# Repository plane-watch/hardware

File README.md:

# Plane Watch hardware

Open hardware designs from Plane Watch for receiving and decoding aircraft surveillance signals.

<div style="text-align: center;"></div>

## Hardware projects

| Project | Preview Image | Description |
| ------- | ------------- | ----------- |
| [ADSBoost](adsboost/README.md) |  | A receive-only, bias-tee-powered low-noise amplifier and SAW filter module for 1,090 MHz ADS-B and Mode S reception. ADSBoost is designed to be installed close to the antenna; the current prototype is awaiting assembly and performance testing. |
| [Plane Watcher](planewatcher/README.md) |  | An open source, hardware-based ADS-B receiver and decoder for the HelloFPGA Smart ZYNQ SL. Plane Watcher combines a dual-stage RF front end, log detector, ADC and GNSS timing to support FPGA message decoding and accurate MLAT timestamping. |

## License

Unless a project or file explicitly states otherwise, all original hardware design files in this repository are licensed under the [CERN Open Hardware Licence Version 2 – Strongly Reciprocal (CERN-OHL-S-2.0)](LICENSE).

The CERN-OHL-S-2.0 permits commercial use, but its reciprocal requirements apply when covered source or products based on it are distributed. Alternative commercial licensing is available for organisations that need different terms.

In short: you may use and modify the designs privately. If you distribute modified source or products based on them, the CERN-OHL-S-2.0 requirements apply.

## Third-party materials disclaimer

This repository may include third-party datasheets, application notes and other technical documentation. These materials remain the copyright of their respective owners, are not covered by the repository's hardware licence, and are included solely to assist development and interoperability of the hardware projects.

If you are a copyright holder and have concerns about material included here, please open an issue or contact the maintainers.

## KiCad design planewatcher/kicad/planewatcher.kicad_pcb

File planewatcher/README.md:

# plane watcher

The **plane watcher** is our attempt at creating an open source, hardware-based ADS-B receiver and decoder. It is a hat/cape/shield for a [HelloFPGA Smart ZYNQ SL](http://www.hellofpga.com/index.php/2023/05/10/smart-zynq-sl/) board.

The goal of the project is to make a reasonably priced yet high-quality ADS-B receiver for hobbyists. It is designed to support accurate MLAT timestamping using GNSS timing and message decoding in the FPGA.

This repository contains the hardware design. The FPGA gateware and software live in the [plane-watch/plane-watcher](https://github.com/plane-watch/plane-watcher) repository.

<div style="text-align: center;"></div>

## Status

Prototype board revision 1.3 is the latest fabricated and tested revision. Production board revision 1.4 is still being refined and has not yet been fabricated or validated.

### Prototype Board Revision 1.2

The first fabricated prototype worked, but had a few issues:

- The SMA connector for the 1090 MHz RF input fouled on the RJ45 Ethernet connector of the FPGA board. For proto 1.3, the RF and GPS antenna connectors have been swapped to U.FL. We will use pigtails to panel-mount SMA connectors.
- The ADL5513 log-detector output was not strong enough to drive the AD8138 ADC driver gain/feedback network directly. Increasing the gain/feedback resistor values from 499 Ω to 4.7 kΩ fixed this on the prototype. In proto 1.3, the ADL5513 output is also buffered.
- We did not have component footprints to tweak the ADL5513 output slope. These have been added to proto 1.3 to allow further refinement if required.
- The 1PPS LED was way too bright on the prototype, so this has been dimmed for proto 1.3.
- The ADL5513 TADJ trimmer network was too high impedance (I should've read the data sheet better) and did not appear to make any difference whatsoever. This has been replaced with a simple voltage divider set to around 0.86 V, in line with the datasheet guidance.

Regardless of the issues, we observed a reception range of approximately 320 km.

### Prototype Board Revision 1.3

In addition to fixing the issues above, proto 1.3 includes some functionality and layout changes:

- More unpopulated component footprints have been added to allow tweaking/refinement:
  - ADL5513 log-detector slope adjustment voltage divider.
  - AD8138 ADC driver feedback capacitors.
  - Five 0402 pi-pad matching networks along the RF path: one on each side of both LNA stages, and one at the ADL5513 RF input. These enable us refine the 1090 MHz matching and compensate for real-world PCB and component parasitics.
    - The first footprint was populated with additional shunt inductance to greatly improve RF performance.
  - Other tweaking footprints along the ADC signal path.
- The ADL5513 log-detector output is buffered by a high-speed ADA4807-1 op-amp for more robust operation with weak signals, and to decouple it from the AD8138 input network.
- The buffered log-detector output is also fed into a first-order low-pass filter at approximately 0.072 Hz to produce a slow-moving analog baseline. This heavily attenuates short ADS-B pulse bursts, but sustained RF traffic can still affect the baseline. The baseline is buffered by an OPA320 and applied to the AD8138 ADC driver input network, offsetting the detector output before digitisation and improving the usable ADC range for weak pulses.
- RF_IN and GPS antenna connectors have been swapped from SMA to U.FL allowing them to be fitted by the manufacturer, making hand assembly easier.
- A software-controlled bias tee has been added. This can supply around 4.5 V to the RF_IN connector, current-limited to approximately 300 mA. LEDs have been added to show whether bias tee is enabled/disabled, and to show if overcurrent disable has been activated.
- A GNSS-disciplined 1PPS timing output has been added. This is a buffered copy of the LEA-M8T TIMEPULSE signal, provided on a 50 Ω source-terminated U.FL connector. The centre pin carries an active-high pulse and the shell is connected to ground. The output is approximately 0 to 4.5 V into a high-impedance load, or approximately 0 to 2 V into a 50 Ω terminated load. The rising edge should be treated as the timing reference.
- Some discrete resistors have been replaced with resistor arrays to reduce the BoM and make hand assembly easier.
- The ADC supply, reference and VOCM networks have been reworked in an attempt to reduce noise, including additional bypassing, ferrite isolation and improved grounding.
- Selectable REFSENSE links allow the ADC input range to be configured for 1 Vpp or 2 Vpp.
- PCB grounding and sensitive-node isolation have been revised with additional via stitching, shorter reference routing and copper keepouts.
- Additional high-frequency bypassing has been added to keep the bias-tee supply side at RF ground.
- Re-routed ADC input differential pair to remove vias/crossovers & remove skew. The ADC output will need to be negated in software.

Compared to proto 1.2 (blue), the range for proto 1.3 (red) has improved by approximately 70km:

Proto 1.3 (red) performance is roughly on-par with a commercial [Jetvision Radarcape](https://radarcape.com) unit (blue):

## Hardware overview

The design has the following main components and interfaces:

| Function | Implementation |
| --- | --- |
| RF input | 1090 MHz ADS-B, U.FL connector |
| RF front end | Two LNA and SAW filter stages |
| Log detector | ADL5513 |
| Baseband buffers | ADA4807-1 fast-path buffer and OPA320 slow-baseline buffer |
| ADC driver | AD8138 |
| ADC | AD9203, 10-bit, up to 40 MSPS |
| GNSS timing | LEA-M8T with FPGA and external 1PPS outputs |
| Bias tee | Software-controlled, approximately 4.5 V at approximately 300 mA with over-current protection |
| Local power | LT3045 low-noise 3.3 V RF/analog supply |
| FPGA carrier | HelloFPGA Smart ZYNQ SL |

## Connections

| Reference | Connection                 | Connector / pinout                                     | Function                                                                                                                    | Voltage and current                                                                                                                                                                                                                                         |
|-----------|----------------------------|--------------------------------------------------------|-----------------------------------------------------------------------------------------------------------------------------|-------------------------------------------------------------------------------------------------------------------------------------------------------------------------------------------------------------------------------------------------------------|
| **J1**    | **1PPS output**            | U.FL; centre = signal, shell = ground                  | Buffered, non-inverting GNSS TIMEPULSE output. Configure for active-high 1PPS with the rising edge as the timing reference. | With a nominal 4.5 V supply: approximately **0–4.5 V into high impedance**, or **0–2.0 V into 50 Ω**, delivering approximately **40 mA while high**. Includes a 49.9 Ω series resistor; total source resistance is approximately 65 Ω including the driver. |
| **J2**    | **1090 MHz RF input**      | U.FL; centre = RF and optional DC bias, shell = ground | Antenna input for the ADS-B receiver; nominal 50 Ω RF interface.                                                            | Software-controlled bias tee supplies approximately **4.5 V** when enabled. Current-limit threshold is approximately **320 mA**. Sustained overload causes latched shutdown.                                                                                |
| **J6**    | **GNSS antenna input**     | U.FL; centre = RF and DC bias, shell = ground          | Antenna input to the LEA-M8T GNSS receiver; nominal 50 Ω RF interface.                                                      | Active-antenna power is provided through the LEA-M8T antenna-supply circuit.                                                                                                                                                                                |
| **J4**    | **FPGA bank 33 interface** | 40-pin header                                          | Carries the ADC sample clock, 10-bit ADC data, overrange indication, RGB LED controls and regulator power-good signal.      | Receives nominal **3.3 V** on pins **37–38** and approximately **4.5 V FPGA_VCC** on pins **39–40**; ground on pins **35–36**. The 4.5 V input feeds the local regulator (for RF and ADC analog side) and 1PPS driver.                                      |
| **J5**    | **FPGA bank 35 interface** | 40-pin header                                          | Carries GNSS serial/control/timing signals, EEPROM I²C, and bias-tee enable/fault signals.                                  | Receives approximately **4.5 V FPGA_VCC** on pins **1–2** and nominal **3.3 V** on pins **3–4**; ground on pins **5–6**. Supplies the bias tee, GNSS and EEPROM circuits. Available current depends on the carrier board.                                   |

## Blinkenlights

The board currently has 8 LEDs, which are used as follows:

| LED  | Type                            | Purpose                                                                                                             |
|------|---------------------------------|---------------------------------------------------------------------------------------------------------------------|
| LED1 | RGB, software controlled        | **System status:**</br>red (FIFO-full latched) > amber (decoder disabled) > green heartbeat (PL alive and clocking) |
| LED2 | RGB, software controlled        | **DF17 activity**</br>green flash per DF17 extended squitter                                                        |
| LED3 | RGB, software controlled        | **DF11/valid**</br>blue flash per DF11 / accepted message                                                           |
| LED4 | RGB, software controlled        | **Decode health**</br>red when invalid DFs outpace accepted messages, else green while messages flow                |
| LED5 | RGB, software controlled        | reserved for PS override (app/feeder status)                                                                        |
| LED6 | "Pink" (looks white), hardwired | 1PPS from GNSS module (when locked)                                                                                 |
| LED7 | Green, hardwired                | Lit when bias-tee enabled                                                                                           |
| LED8 | Red, hardwired                  | Bias-tee over-current shutdown or thermal shutdown                                                                  |

## Design

The design consists of the following parts:

### RF Input

The signal from the antenna is amplified and filtered using two stages of LNA amplification and SAW filters centred on 1090 MHz.

A switchable bias tee power supply can apply approximately 4.5 V at up to approximately 300 mA to the RF_IN connector.

LED7 (green) indicates bias-tee is enabled.
LED8 (red) indicates an overcurrent shutdown of bias-tee.

### Log Detector

The amplified and filtered RF signal is fed into an ADL5513 log detector, which produces a voltage proportional to the logarithm of the RF input power. With an oscilloscope on its output, we can see the raw ADS-B pulses and decode them by hand.

### ADC Driver

The ADL5513 log-detector output is buffered with a high-speed ADA4807-1 op-amp to isolate it from the ADC driver input network and provide a robust baseband signal. Without the buffer, the output of the log detector is too weak for the gain/feedback network surrounding the AD8138.

The ADC uses a differential input. To drive it, the buffered baseband signal is split:

- Through the gain/input resistor network into the AD8138 positive input summing node.
- Into a first-order low-pass filter at approximately 0.072 Hz, producing a slow-moving analog baseline with short ADS-B pulse bursts heavily attenuated. This baseline is then buffered by an OPA320 to decouple it from the ADC driver input network and applied through the gain/input resistor network into the AD8138 negative input summing node.

The AD8138 produces a differential output proportional to the difference between the instantaneous log-detector output and the slow noise-floor estimate.

### ADC

The differential output of the ADC driver is fed into an AD9203 10-bit, 40 MSPS ADC. The ADC input range can be configured for 1 Vpp or 2 Vpp using selectable REFSENSE links. By default, 2 Vpp is used to give the largest dynamic range. The FPGA supplies the sample clock and receives the digitised output.

### GNSS Timing

The LEA-M8T GNSS timing receiver provides its TIMEPULSE signal to the FPGA for timestamping. Proto 1.3 also buffers this signal for an external, source-terminated 1PPS output and a status LED (LED6).

### EEPROM

The board contains a 16K I²C EEPROM. The EEPROM data is written once at assembly time and read back at boot-time to set board details such as MAC address, serial number, credentials, etc.

### Power

The power supplies are split in an attempt to reduce noise on the RF & ADC supply.

#### RF & ADC

The RF and analog ADC sections are powered from the approximately 4.5 V FPGA_VCC rail provided by the carrier board (5V from the USB-C connector, through a Schottky diode). The input has resettable overcurrent and transient protection. A ferrite-filtered LT3045-1 linear regulator generates the local low-noise 3.3 V RF/analog supply, with additional ferrite isolation and local bypassing around the ADC.

The ADC digital power is fed directly from the FPGA board 3V3 rail.

#### Bias-Tee, GNSS & EEPROM

These are powered directly from the FPGA board:

- Bias-Tee current is supplied by the approximately 4.5 V FPGA_VCC rail
- The GNSS module is powered directly from the FPGA board 3V3 rail. The 1PPS output is powered from the approximately 4.5 V FPGA_VCC rail via a MOSFET driver.
- The EEPROM is powered directly from the FPGA board 3V3 rail.

### FPGA

The FPGA gateware samples the ADC output, detects and timestamps ADS-B pulses, and converts them into usable messages. The gateware and supporting software are developed in the [plane-watch/plane-watcher](https://github.com/plane-watch/plane-watcher) repository.

## Attributions

- [“1.09 GHz Mode-S Receiver Design and
  VHF Radar Antenna Characterization”, Senior Thesis in Electrical Engineering, Dabin Zhang](https://www.ideals.illinois.edu/items/47640/bitstreams/139976/data.pdf).
- [Project “ADS-B Receiver and Decoder” presentation by Günter Köllner, DL4MEA](https://www.qsl.net/dl4mea/fpgaadsb/Koellner_Projekt-ADSB3.pdf).
- The [Open Source Hardware gear logo](https://oshwa.org/resources/open-source-hardware-logo/) was designed by Macklin Chaffee and is licensed CC-SA.
- “Dickbutt” appears courtesy of [K.C. Green](https://kcgreendotcom.com/). RF performance gains are unverified.

## License

The hardware design files are licensed under the [CERN Open Hardware Licence Version 2 – Strongly Reciprocal (CERN-OHL-S-2.0)](LICENSE).

The CERN-OHL-S-2.0 permits commercial use, but its reciprocal requirements apply when covered source or products based on it are distributed.

Alternative commercial licensing is available for companies that need different terms.

TL;DR: You can use and modify the design privately. If you distribute modified source or products based on it, the CERN-OHL-S-2.0 requirements apply. If those terms do not work for you, talk to us.

## Notice

This repository may include third-party datasheets, application notes, and technical documentation.

Such materials remain the copyright of their respective owners and are included solely to assist development and interoperability of this project.

If you are a copyright holder and have concerns regarding included materials, please open an issue or contact the maintainers.

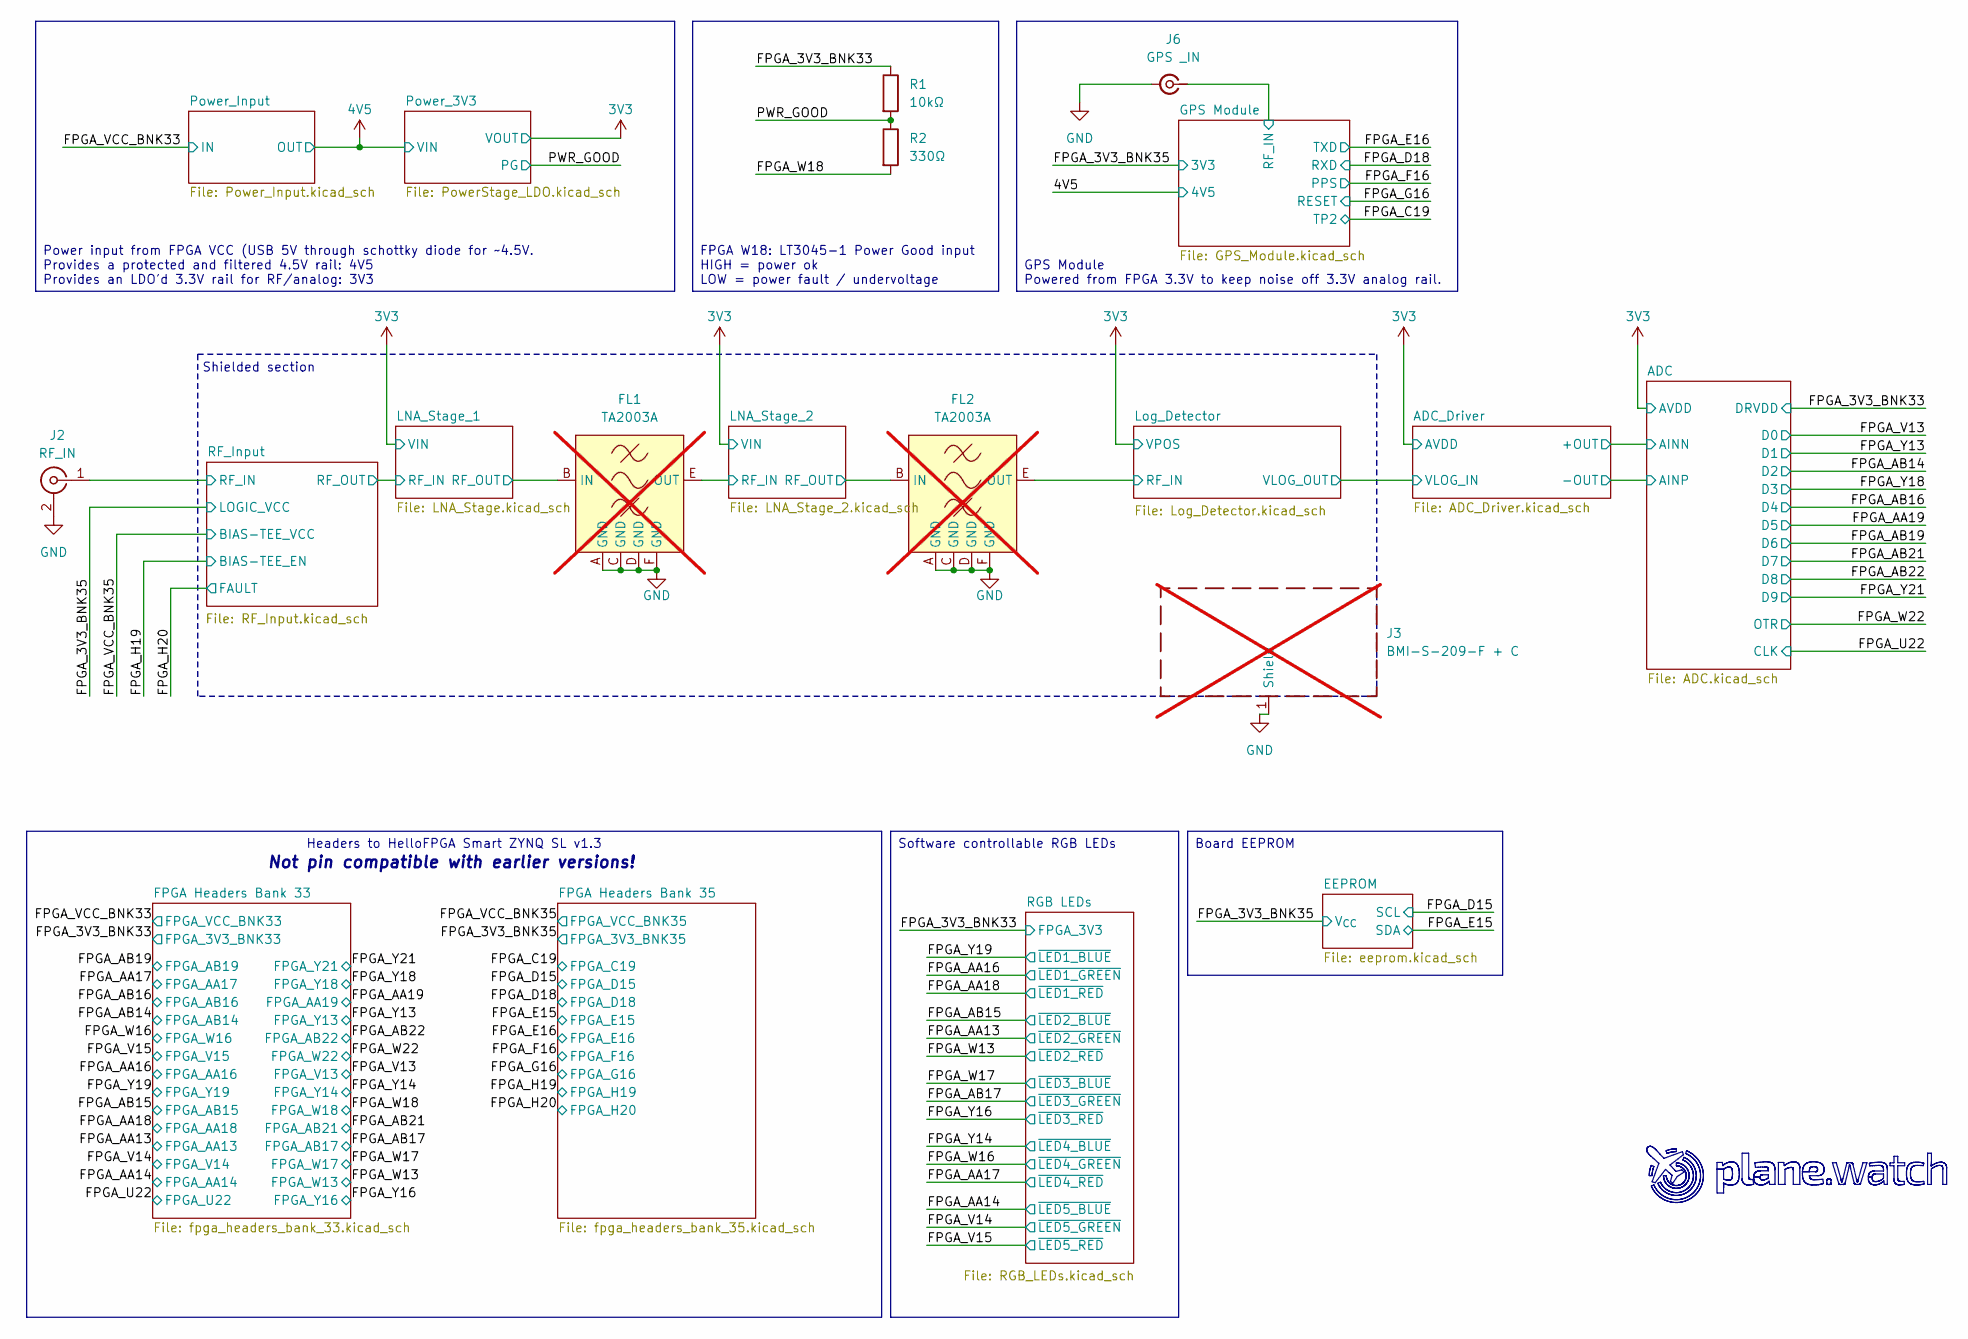
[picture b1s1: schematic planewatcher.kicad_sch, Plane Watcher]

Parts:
FL1, FL2: TA2003A; FL_Tai-Saw_TA2003A; MPN TA2003A; not fitted
J2: RF_IN; U.FL_Hirose_U.FL-R-SMT-1_Vertical; MPN U.FL-R-SMT-1; LCSC C88374
J3: BMI-S-209-F + C; Laird_Technologies_BMI-S-209-F_29.36x18.50mm; MPN BMI-S-209-F + BMI-S-209-C; not fitted
J6: GPS _IN; U.FL_Hirose_U.FL-R-SMT-1_Vertical; MPN U.FL-R-SMT-1; LCSC C88374
R1: 10kΩ; R_0402_1005Metric; MPN ERA-2AEB103X; LCSC C191915
R2: 330Ω; R_0402_1005Metric; MPN RT0402FRE07330RL; LCSC C854274

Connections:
/FPGA_3V3_BNK33: R1.1; also elsewhere on the board
/FPGA_W18: R2.2; also elsewhere on the board
/GPS Module/RF_IN: J6.1 (In); also elsewhere on the board
/LNA_Stage_1/RF_OUT: FL1.B (IN); also elsewhere on the board
/LNA_Stage_2/RF_IN: FL1.E (OUT); also elsewhere on the board
/LNA_Stage_2/RF_OUT: FL2.B (IN); also elsewhere on the board
/Log_Detector/RF_IN: FL2.E (OUT); also elsewhere on the board
/PWR_GOOD: R1.2, R2.1; also elsewhere on the board
/RF_Input/RF_IN: J2.1 (In); also elsewhere on the board
GND: FL1.A (GND), FL1.C (GND), FL1.D (GND), FL1.F (GND), FL2.A (GND), FL2.C (GND), FL2.D (GND), FL2.F (GND), J2.2 (Ext), J3.1 (Shield_1), J6.2 (Ext); also elsewhere on the board

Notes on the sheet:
Shielded section
Not pin compatible with earlier versions!
Board EEPROM
FPGA W18: LT3045-1 Power Good input HIGH = power ok LOW = power fault / undervoltage
Power input from FPGA VCC (USB 5V through schottky diode for ~4.5V. Provides a protected and filtered 4.5V rail: 4V5 Provides an LDO'd 3.3V rail for RF/analog: 3V3
GPS Module Powered from FPGA 3.3V to keep noise off 3.3V analog rail.
Headers to HelloFPGA Smart ZYNQ SL v1.3
Software controllable RGB LEDs

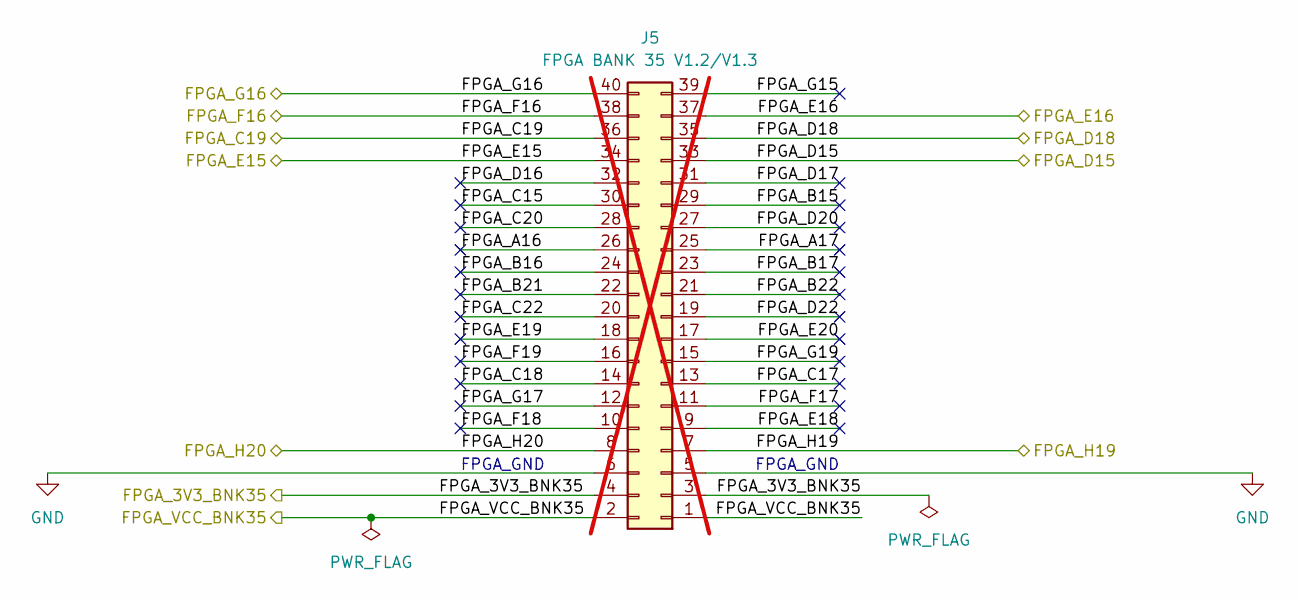
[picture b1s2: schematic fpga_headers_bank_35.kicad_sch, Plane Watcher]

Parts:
J5: FPGA BANK 35 V1.2/V1.3; PinHeader_2x20_P2.54mm_Vertical; MPN TSW-120-07-L-D; LCSC C5968215; not fitted

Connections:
/FPGA Headers Bank 35/FPGA_A16: J5.26
/FPGA Headers Bank 35/FPGA_A17: J5.25
/FPGA Headers Bank 35/FPGA_B15: J5.29
/FPGA Headers Bank 35/FPGA_B16: J5.24
/FPGA Headers Bank 35/FPGA_B17: J5.23
/FPGA Headers Bank 35/FPGA_B21: J5.22
/FPGA Headers Bank 35/FPGA_B22: J5.21
/FPGA Headers Bank 35/FPGA_C15: J5.30
/FPGA Headers Bank 35/FPGA_C17: J5.13
/FPGA Headers Bank 35/FPGA_C18: J5.14
/FPGA Headers Bank 35/FPGA_C20: J5.28
/FPGA Headers Bank 35/FPGA_C22: J5.20
/FPGA Headers Bank 35/FPGA_D16: J5.32
/FPGA Headers Bank 35/FPGA_D17: J5.31
/FPGA Headers Bank 35/FPGA_D20: J5.27
/FPGA Headers Bank 35/FPGA_D22: J5.19
/FPGA Headers Bank 35/FPGA_E18: J5.9
/FPGA Headers Bank 35/FPGA_E19: J5.18
/FPGA Headers Bank 35/FPGA_E20: J5.17
/FPGA Headers Bank 35/FPGA_F17: J5.11
/FPGA Headers Bank 35/FPGA_F18: J5.10
/FPGA Headers Bank 35/FPGA_F19: J5.16
/FPGA Headers Bank 35/FPGA_G15: J5.39
/FPGA Headers Bank 35/FPGA_G17: J5.12
/FPGA Headers Bank 35/FPGA_G19: J5.15
/FPGA_3V3_BNK35: J5.3, J5.4; also elsewhere on the board
/FPGA_C19: J5.36; also elsewhere on the board
/FPGA_D15: J5.33; also elsewhere on the board
/FPGA_D18: J5.35; also elsewhere on the board
/FPGA_E15: J5.34; also elsewhere on the board
/FPGA_E16: J5.37; also elsewhere on the board
/FPGA_F16: J5.38; also elsewhere on the board
/FPGA_G16: J5.40; also elsewhere on the board
/FPGA_H19: J5.7; also elsewhere on the board
/FPGA_H20: J5.8; also elsewhere on the board
/FPGA_VCC_BNK35: J5.1, J5.2; also elsewhere on the board
GND: J5.5, J5.6; also elsewhere on the board

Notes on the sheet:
FPGA_GND

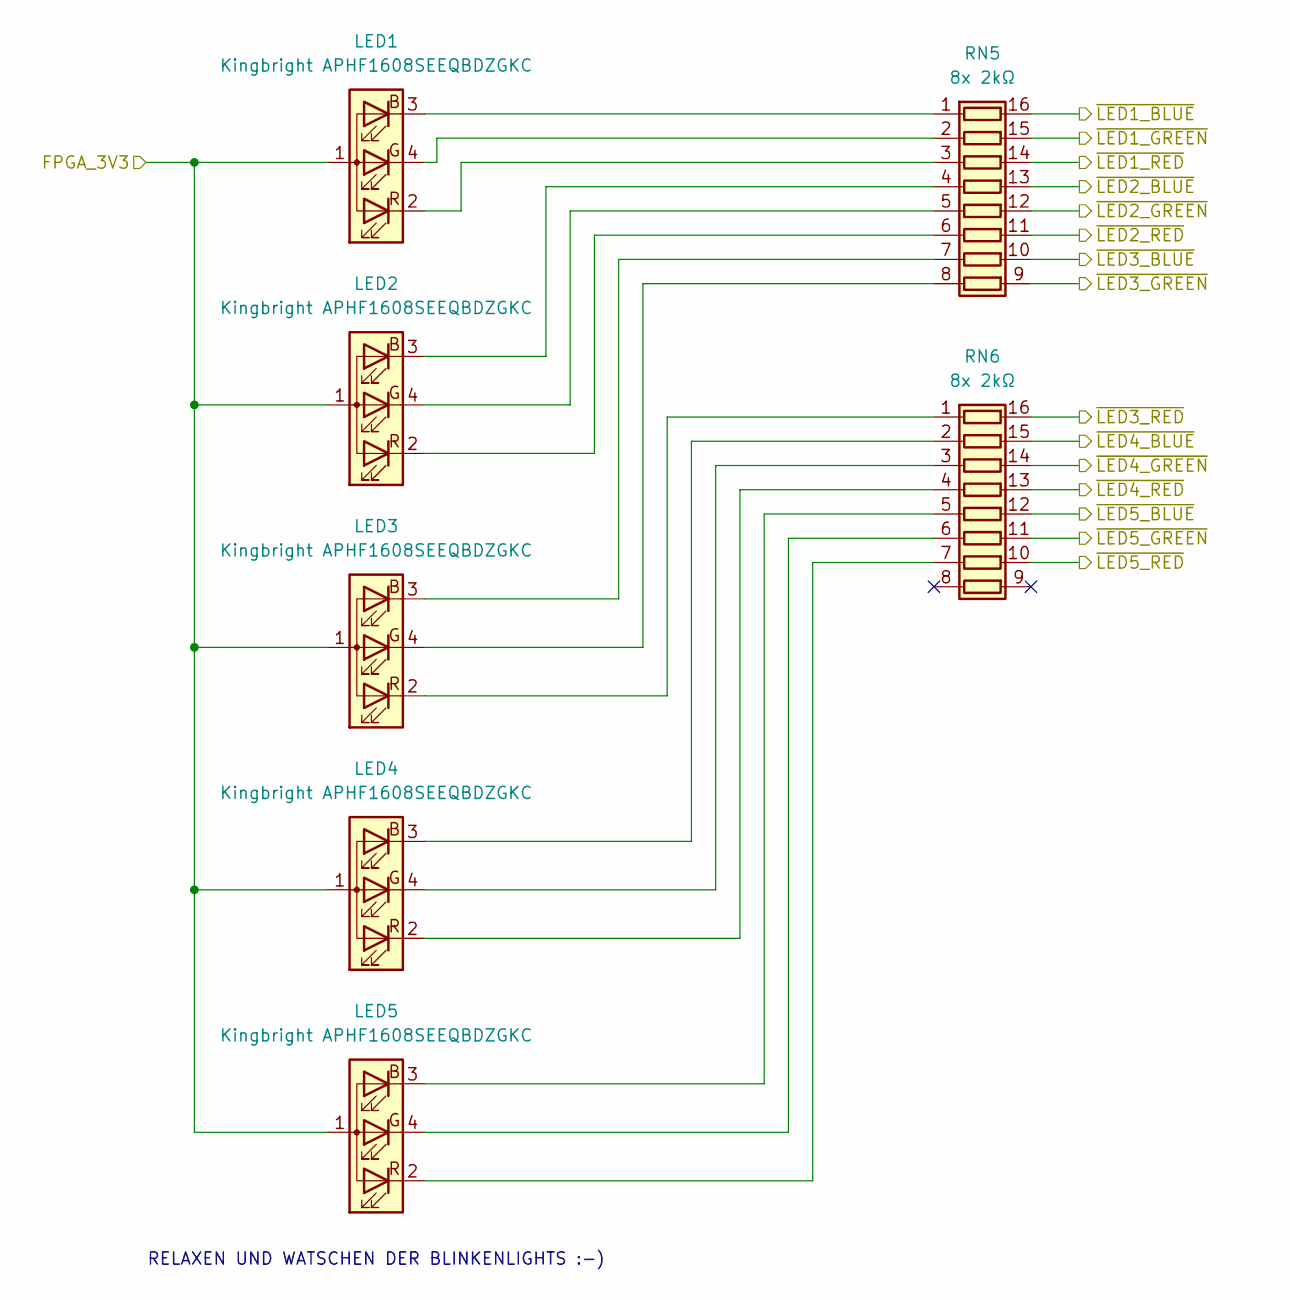
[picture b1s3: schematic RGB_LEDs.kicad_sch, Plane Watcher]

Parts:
LED1, LED2, LED3, LED4, LED5: Kingbright APHF1608SEEQBDZGKC; LED_Kingbright_APHF1608SEEQBDZGKC; MPN APHF1608SEEQBDZGKC; LCSC C5145179
RN5, RN6: 8x 2kΩ; 8x0402; MPN YC248-JR-072KL; LCSC C874618

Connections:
/FPGA_3V3_BNK33: LED1.1 (A), LED2.1 (A), LED3.1 (A), LED4.1 (A), LED5.1 (A); also elsewhere on the board
/FPGA_AA13: RN5.12 (R5.2); also elsewhere on the board
/FPGA_AA14: RN6.12 (R5.2); also elsewhere on the board
/FPGA_AA16: RN5.15 (R2.2); also elsewhere on the board
/FPGA_AA17: RN6.13 (R4.2); also elsewhere on the board
/FPGA_AA18: RN5.14 (R3.2); also elsewhere on the board
/FPGA_AB15: RN5.13 (R4.2); also elsewhere on the board
/FPGA_AB17: RN5.9 (R8.2); also elsewhere on the board
/FPGA_V14: RN6.11 (R6.2); also elsewhere on the board
/FPGA_V15: RN6.10 (R7.2); also elsewhere on the board
/FPGA_W13: RN5.11 (R6.2); also elsewhere on the board
/FPGA_W16: RN6.14 (R3.2); also elsewhere on the board
/FPGA_W17: RN5.10 (R7.2); also elsewhere on the board
/FPGA_Y14: RN6.15 (R2.2); also elsewhere on the board
/FPGA_Y16: RN6.16 (R1.2); also elsewhere on the board
/FPGA_Y19: RN5.16 (R1.2); also elsewhere on the board
unnamed: LED1.3 (BK), RN5.1 (R1.1)
unnamed: LED1.4 (GK), RN5.2 (R2.1)
unnamed: LED1.2 (RK), RN5.3 (R3.1)
unnamed: LED2.3 (BK), RN5.4 (R4.1)
unnamed: LED2.4 (GK), RN5.5 (R5.1)
unnamed: LED2.2 (RK), RN5.6 (R6.1)
unnamed: LED3.3 (BK), RN5.7 (R7.1)
unnamed: LED3.4 (GK), RN5.8 (R8.1)
unnamed: LED3.2 (RK), RN6.1 (R1.1)
unnamed: LED4.3 (BK), RN6.2 (R2.1)
unnamed: LED4.4 (GK), RN6.3 (R3.1)
unnamed: LED4.2 (RK), RN6.4 (R4.1)
unnamed: LED5.3 (BK), RN6.5 (R5.1)
unnamed: LED5.4 (GK), RN6.6 (R6.1)
unnamed: LED5.2 (RK), RN6.7 (R7.1)

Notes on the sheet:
RELAXEN UND WATSCHEN DER BLINKENLIGHTS :-)

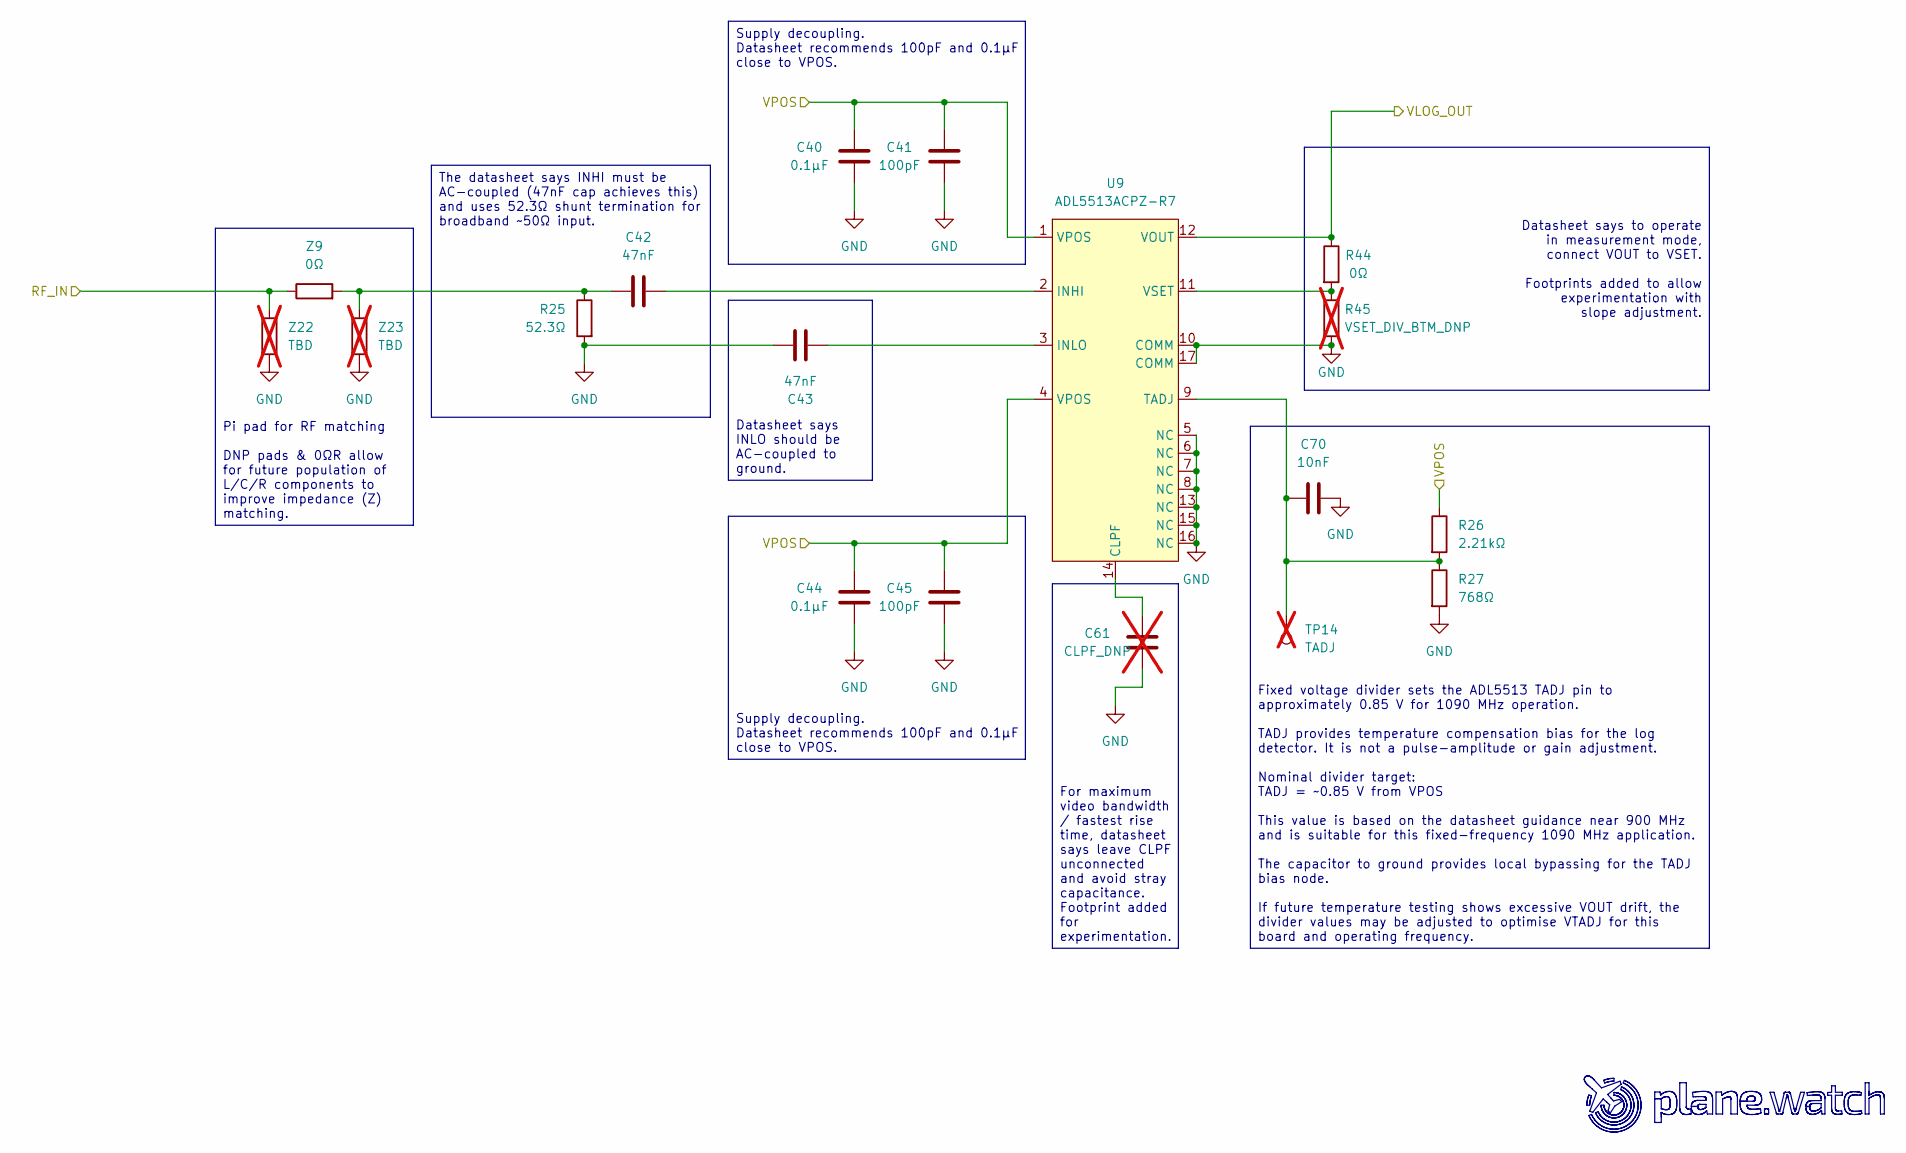
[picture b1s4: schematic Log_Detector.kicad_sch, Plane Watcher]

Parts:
C40, C44: 0.1µF; C_0402_1005Metric; MPN GCM155R71A104KA55D; LCSC C161163
C41, C45: 100pF; C_0402_1005Metric; MPN GCM1555C1H101FA16D; LCSC C2941926
C42, C43: 47nF; C_0402_1005Metric; MPN CC0402KRX7R6BB473; LCSC C327054
C61: CLPF_DNP; C_0402_1005Metric; MPN GCM1555C1H101FA16D; LCSC C2941926; not fitted
C70: 10nF; C_0402_1005Metric; MPN CL05B103KB5NNNC; LCSC C15195
R25: 52.3Ω; R_0402_1005Metric; MPN RC0402FR-0752R3L; LCSC C273696
R26: 2.21kΩ; R_0402_1005Metric; MPN ERJ2RKF2211X; LCSC C416496
R27: 768Ω; R_0402_1005Metric; MPN ERJ2RKF7680X; LCSC C3025660
R44: 0Ω; R_0402_1005Metric; MPN ERJ-2GE0R00X; LCSC C242160
R45: VSET_DIV_BTM_DNP; R_0402_1005Metric; not fitted
TP14: TADJ; TestPoint_THTPad_D1.0mm_Drill0.5mm; not fitted
U9: ADL5513ACPZ-R7; LFCSP-16-1EP_3x3mm_P0.5mm_EP1.6x1.6mm; MPN ADL5513ACPZ-R7; LCSC C579160
Z9: 0Ω; R_0402_1005Metric; MPN ERJ-2GE0R00X; LCSC C242160
Z22, Z23: TBD; R_0402_1005Metric; not fitted

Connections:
3V3: C40.2, C41.2, C44.2, C45.2, R26.1, U9.1 (VPOS), U9.4 (VPOS); also elsewhere on the board
/ADC_Driver/VLOG_IN: R44.1, U9.12 (VOUT); also elsewhere on the board
/Log_Detector/RF_IN: Z9.1, Z22.2; also elsewhere on the board
GND: C40.1, C41.1, C43.2, C44.1, C45.1, C61.1, C70.2, R25.2, R27.2, R45.2, U9.5 (NC), U9.6 (NC), U9.7 (NC), U9.8 (NC), U9.10 (COMM), U9.13 (NC), U9.15 (NC), U9.16 (NC), U9.17 (COMM), Z22.1, Z23.1; also elsewhere on the board
unnamed: C42.1, R25.1, Z9.2, Z23.2
unnamed: C61.2, U9.14 (CLPF)
unnamed: C42.2, U9.2 (INHI)
unnamed: C43.1, U9.3 (INLO)
unnamed: C70.1, R26.2, R27.1, TP14.1 (1_1), U9.9 (TADJ)
unnamed: R44.2, R45.1, U9.11 (VSET)

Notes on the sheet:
Supply decoupling. Datasheet recommends 100pF and 0.1µF close to VPOS.
The datasheet says INHI must be AC-coupled (47nF cap achieves this) and uses 52.3Ω shunt termination for broadband ~50Ω input.
Datasheet says to operate in measurement mode, connect VOUT to VSET. Footprints added to allow experimentation with slope adjustment.
Datasheet says INLO should be AC-coupled to ground.
Fixed voltage divider sets the ADL5513 TADJ pin to approximately 0.85 V for 1090 MHz operation. TADJ provides temperature compensation bias for the log detector. It is not a pulse-amplitude or gain adjustment. Nominal divider target: TADJ = ~0.85 V from VPOS This value is based on the datasheet gui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
Pi pad for RF matching DNP pads & 0ΩR allow for future population of L/C/R components to improve impedance (Z) matching.
For maximum video bandwidth / fastest rise time, datasheet says leave CLPF unconnected and avoid stray capacitance. Footprint added for experimentation.

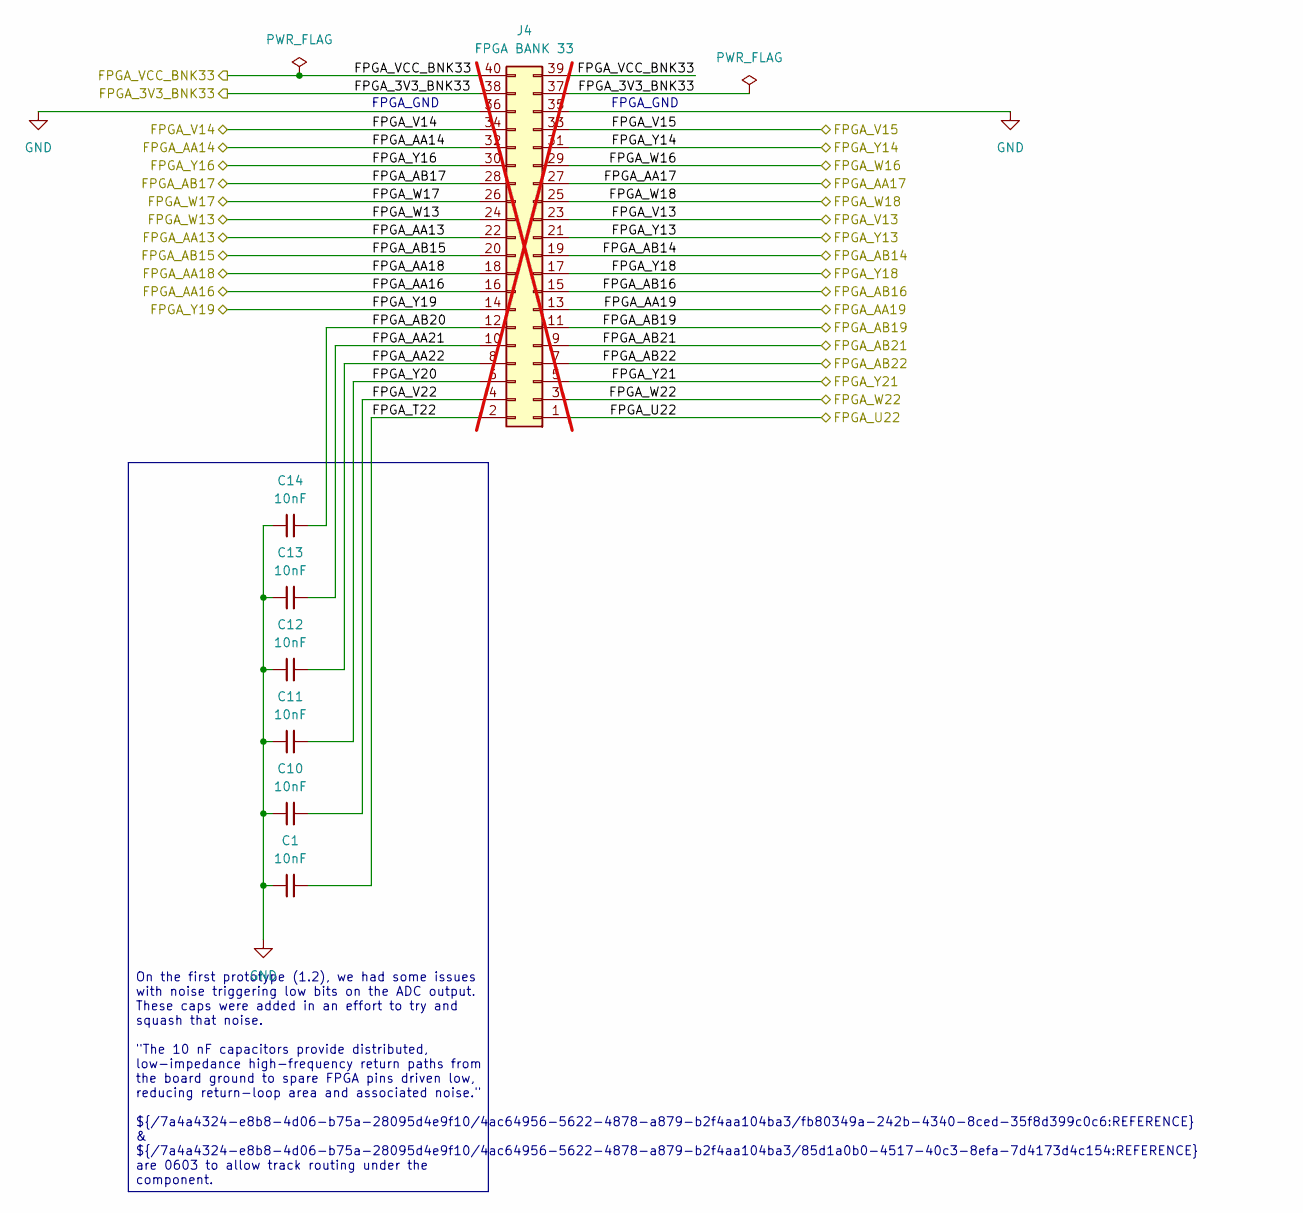
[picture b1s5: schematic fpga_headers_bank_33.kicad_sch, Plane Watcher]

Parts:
C1, C10, C13, C14: 10nF; C_0402_1005Metric; MPN GRM1555C1E103JE01D; LCSC C3855387
C11, C12: 10nF; C_0603_1608Metric; MPN GRM1885C1H103JA01D; LCSC C85973
J4: FPGA BANK 33; PinHeader_2x20_P2.54mm_Vertical; MPN TSW-120-07-L-D; LCSC C5968215; not fitted

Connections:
/FPGA Headers Bank 33/FPGA_AA21: C13.1, J4.10
/FPGA Headers Bank 33/FPGA_AA22: C12.1, J4.8
/FPGA Headers Bank 33/FPGA_AB20: C14.1, J4.12
/FPGA Headers Bank 33/FPGA_T22: C1.1, J4.2
/FPGA Headers Bank 33/FPGA_V22: C10.1, J4.4
/FPGA Headers Bank 33/FPGA_Y20: C11.1, J4.6
/FPGA_3V3_BNK33: J4.37, J4.38; also elsewhere on the board
/FPGA_AA13: J4.22; also elsewhere on the board
/FPGA_AA14: J4.32; also elsewhere on the board
/FPGA_AA16: J4.16; also elsewhere on the board
/FPGA_AA17: J4.27; also elsewhere on the board
/FPGA_AA18: J4.18; also elsewhere on the board
/FPGA_AA19: J4.13; also elsewhere on the board
/FPGA_AB14: J4.19; also elsewhere on the board
/FPGA_AB15: J4.20; also elsewhere on the board
/FPGA_AB16: J4.15; also elsewhere on the board
/FPGA_AB17: J4.28; also elsewhere on the board
/FPGA_AB19: J4.11; also elsewhere on the board
/FPGA_AB21: J4.9; also elsewhere on the board
/FPGA_AB22: J4.7; also elsewhere on the board
/FPGA_U22: J4.1; also elsewhere on the board
/FPGA_V13: J4.23; also elsewhere on the board
/FPGA_V14: J4.34; also elsewhere on the board
/FPGA_V15: J4.33; also elsewhere on the board
/FPGA_VCC_BNK33: J4.39, J4.40; also elsewhere on the board
/FPGA_W13: J4.24; also elsewhere on the board
/FPGA_W16: J4.29; also elsewhere on the board
/FPGA_W17: J4.26; also elsewhere on the board
/FPGA_W18: J4.25; also elsewhere on the board
/FPGA_W22: J4.3; also elsewhere on the board
/FPGA_Y13: J4.21; also elsewhere on the board
/FPGA_Y14: J4.31; also elsewhere on the board
/FPGA_Y16: J4.30; also elsewhere on the board
/FPGA_Y18: J4.17; also elsewhere on the board
/FPGA_Y19: J4.14; also elsewhere on the board
/FPGA_Y21: J4.5; also elsewhere on the board
GND: C1.2, C10.2, C11.2, C12.2, C13.2, C14.2, J4.35, J4.36; also elsewhere on the board

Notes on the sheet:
FPGA_GND
On the first prototype (1.2), we had some issues with noise triggering low bits on the ADC output. These caps were added in an effort to try and squash that noise. "The 10 nF capacitors provide distributed, low-impedance high-frequency return paths from the board ground to spare FPGA pins driven lo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

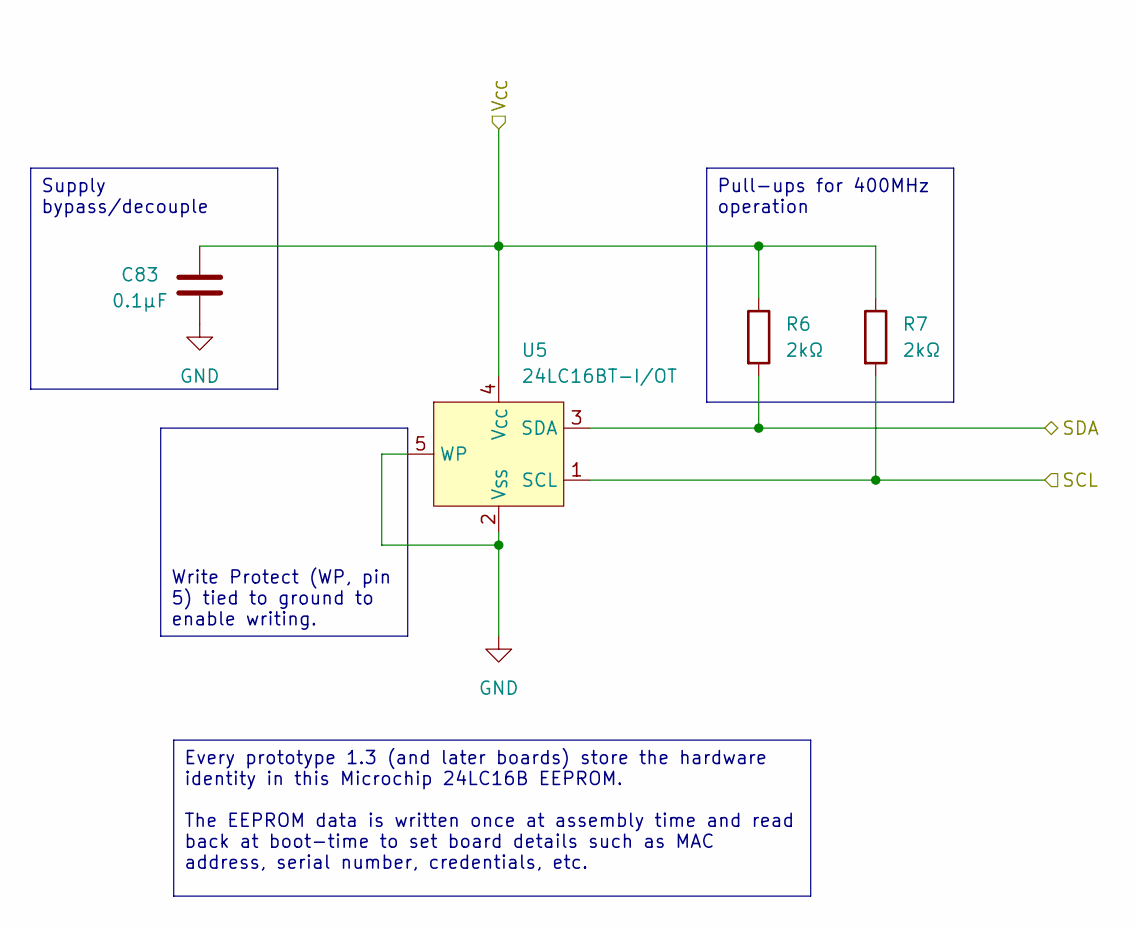
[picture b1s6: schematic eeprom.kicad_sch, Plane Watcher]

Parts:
C83: 0.1µF; C_0402_1005Metric; MPN GCM155R71A104KA55D; LCSC C161163
R6, R7: 2kΩ; R_0402_1005Metric; MPN ERJ2RKF2001X; LCSC C413086
U5: 24LC16BT-I/OT; SOT-23-5; MPN 24LC16BT-I/OT; LCSC C2061286

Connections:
/FPGA_3V3_BNK35: C83.1, R6.1, R7.1, U5.4 (V_{CC}); also elsewhere on the board
/FPGA_D15: R7.2, U5.1 (SCL); also elsewhere on the board
/FPGA_E15: R6.2, U5.3 (SDA); also elsewhere on the board
GND: C83.2, U5.2 (V_{SS}), U5.5 (WP); also elsewhere on the board

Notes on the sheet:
Pull-ups for 400MHz operation
Supply bypass/decouple
Write Protect (WP, pin 5) tied to ground to enable writing.
Every prototype 1.3 (and later boards) store the hardware identity in this Microchip 24LC16B EEPROM. The EEPROM data is written once at assembly time and read back at boot-time to set board details such as MAC address, serial number, credentials, etc.

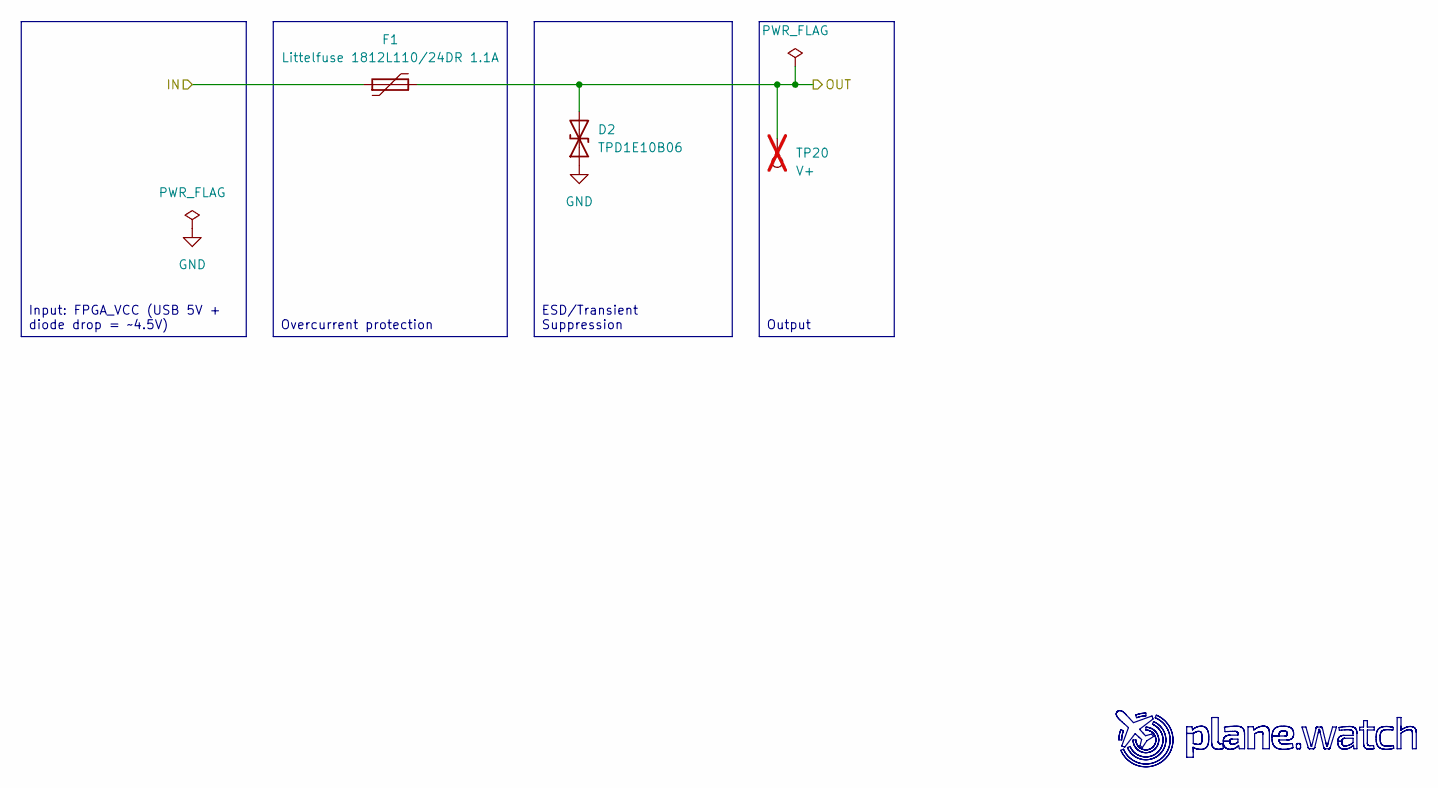
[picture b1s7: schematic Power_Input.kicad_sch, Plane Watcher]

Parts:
D2: TPD1E10B06; D_SOD-523; MPN TPD1E10B06DYAR; LCSC C3712135
F1: Littelfuse 1812L110/24DR 1.1A; Fuse_1812_4532Metric; MPN 1812L110/24DR; LCSC C207066
TP20: V+; TestPoint_THTPad_D1.0mm_Drill0.5mm; not fitted

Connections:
4V5: D2.2 (A2), F1.2, TP20.1 (1_1); also elsewhere on the board
/FPGA_VCC_BNK33: F1.1; also elsewhere on the board
GND: D2.1 (A1); also elsewhere on the board

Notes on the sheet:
Overcurrent protection
ESD/Transient Suppression
Input: FPGA_VCC (USB 5V + diode drop = ~4.5V)
Output

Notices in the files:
adsboost/kicad/adsboost.kicad_pcb:
License: CERN-OHL-S-2.0
planewatcher/kicad/ADC.kicad_sch:
No warranty; see LICENSE.
Licensed under CERN-OHL-S-2.0.
Copyright (C) 2026 plane.watch team and contributors.
planewatcher/kicad/planewatcher.kicad_pcb:
© 2026 plane.watch team
